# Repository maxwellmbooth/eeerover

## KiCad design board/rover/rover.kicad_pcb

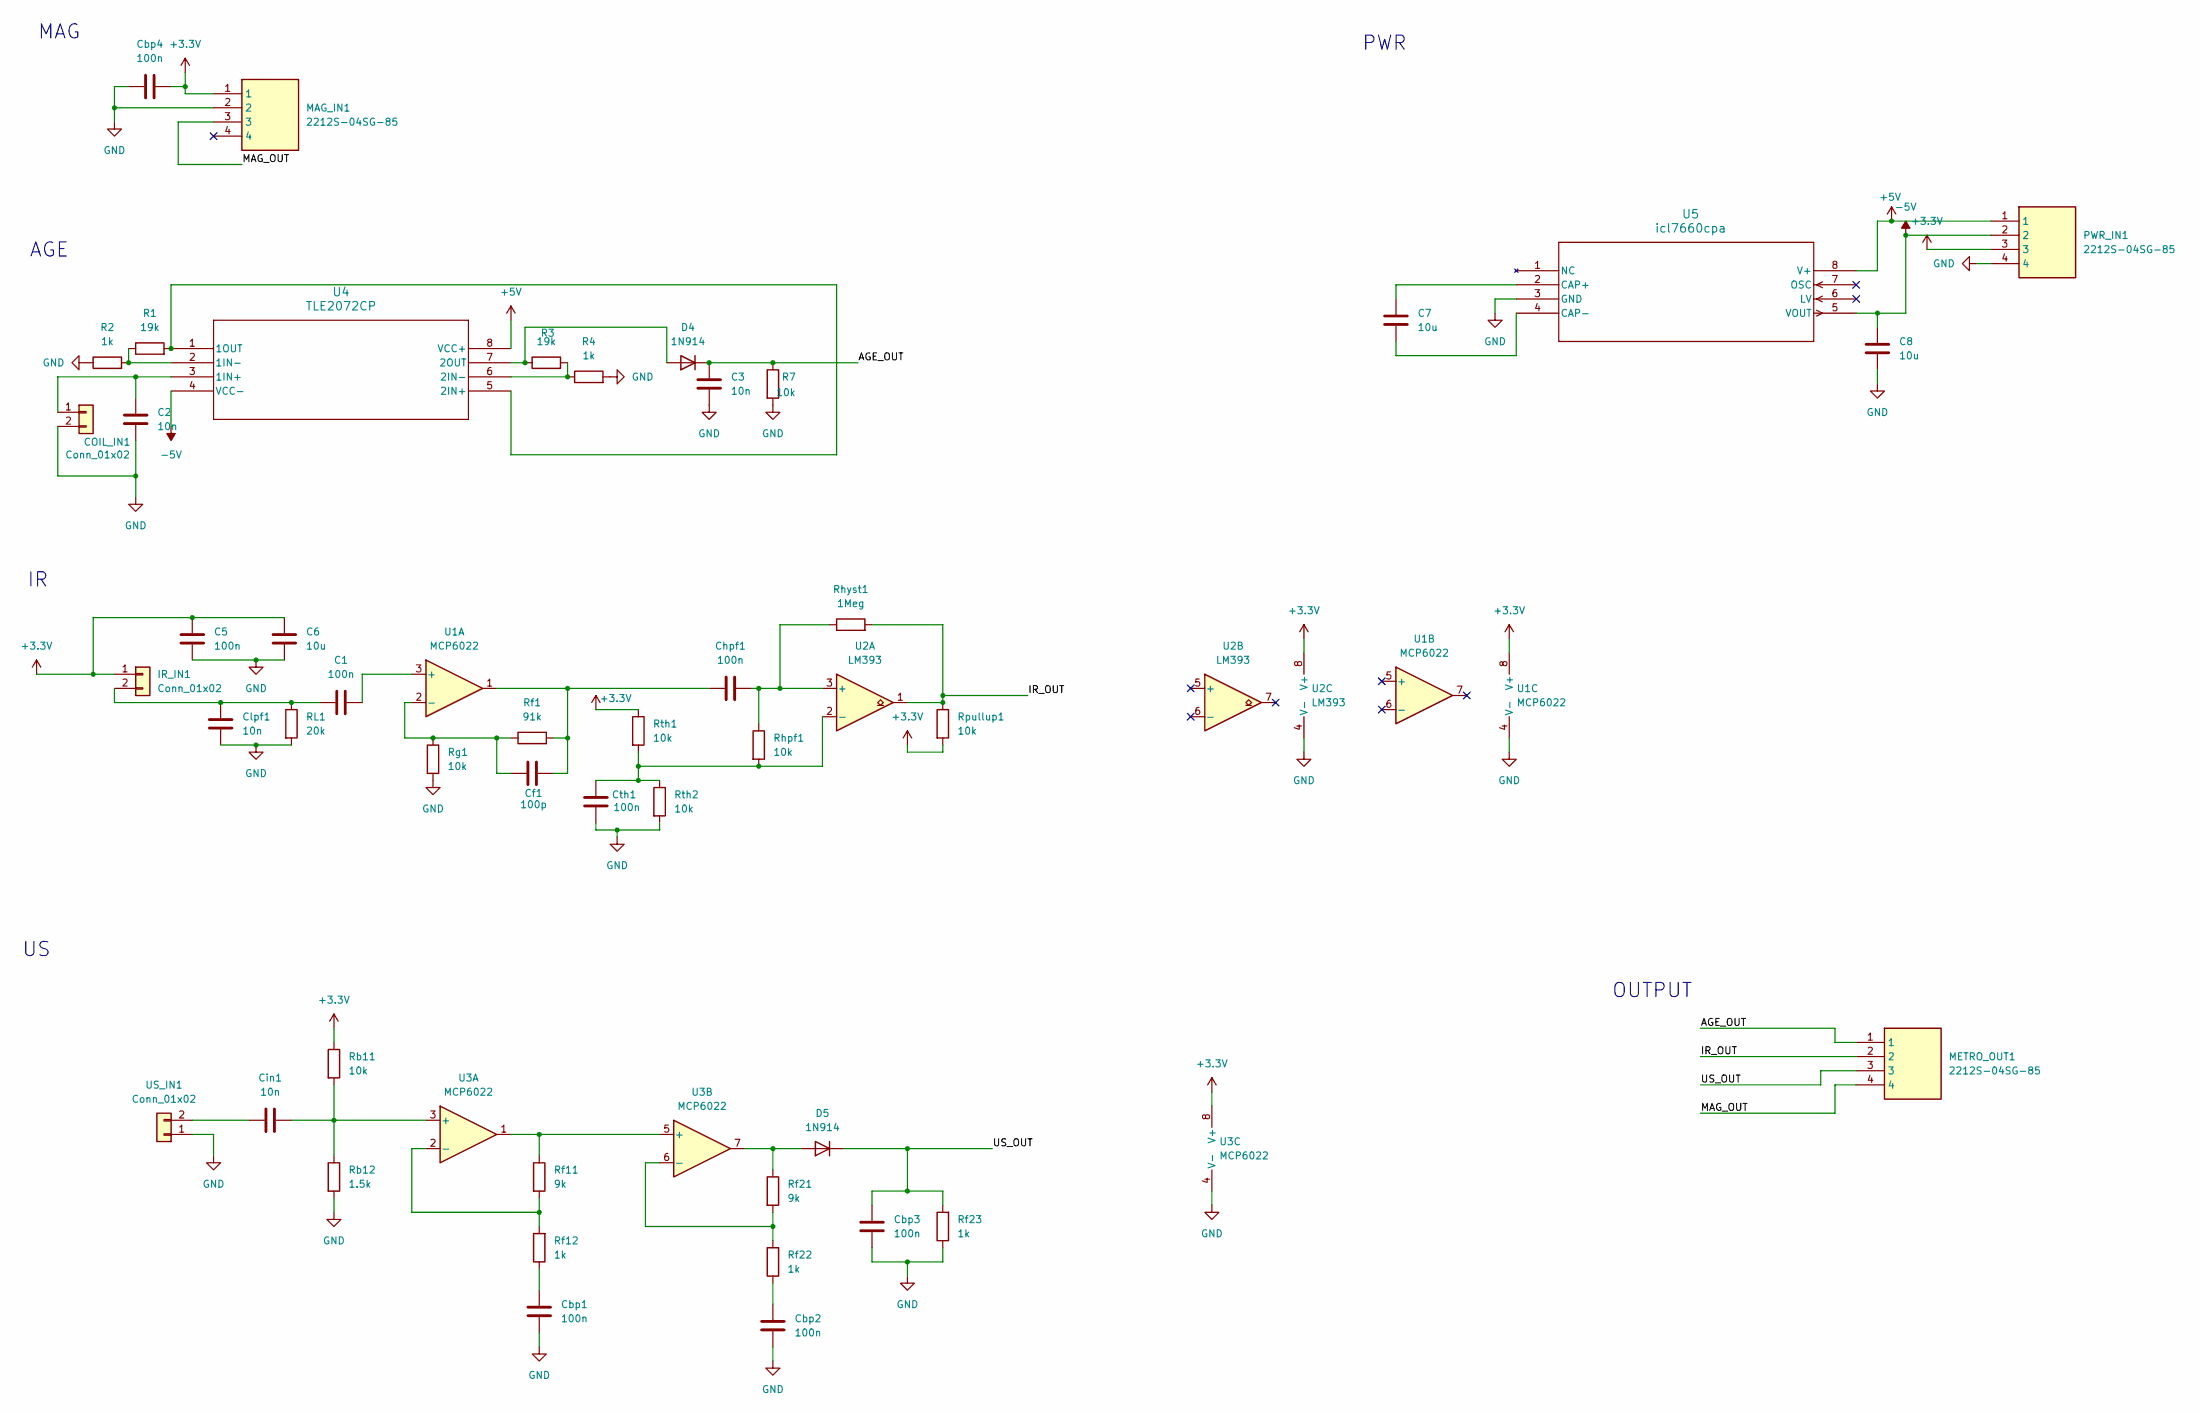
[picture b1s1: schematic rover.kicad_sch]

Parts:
C1, C5: 100n; C_Disc_D5.0mm_W2.5mm_P2.50mm
C2, C3: 10n; C_Disc_D5.0mm_W2.5mm_P2.50mm
C6, C7, C8: 10u; CP_Radial_D5.0mm_P2.50mm
COIL_IN1: Conn_01x02; TerminalBlock_MaiXu_MX126-5.0-02P_1x02_P5.00mm
Cbp1, Cbp2, Cbp3, Cbp4: 100n; C_Disc_D5.0mm_W2.5mm_P2.50mm
Cf1: 100p; C_Disc_D5.0mm_W2.5mm_P2.50mm
Chpf1: 100n; C_Disc_D5.0mm_W2.5mm_P2.50mm
Cin1: 10n; C_Disc_D5.0mm_W2.5mm_P2.50mm
Clpf1: 10n; C_Disc_D5.0mm_W2.5mm_P2.50mm
Cth1: 100n; C_Disc_D5.0mm_W2.5mm_P2.50mm
D4, D5: 1N914; D_DO-35_SOD27_P7.62mm_Horizontal
IR_IN1: Conn_01x02; TerminalBlock_MaiXu_MX126-5.0-02P_1x02_P5.00mm
MAG_IN1: 2212S-04SG-85; 2212S04SG85; Manufacturer_Part_Number 2212S-04SG-85
METRO_OUT1: 2212S-04SG-85; 2212S04SG85; Manufacturer_Part_Number 2212S-04SG-85
PWR_IN1: 2212S-04SG-85; 2212S04SG85; Manufacturer_Part_Number 2212S-04SG-85
R1, R3: 19k; R_Axial_DIN0207_L6.3mm_D2.5mm_P10.16mm_Horizontal
R2, R4: 1k; R_Axial_DIN0207_L6.3mm_D2.5mm_P10.16mm_Horizontal
R7: 10k; R_Axial_DIN0207_L6.3mm_D2.5mm_P10.16mm_Horizontal
RL1: 20k; R_Axial_DIN0207_L6.3mm_D2.5mm_P10.16mm_Horizontal
Rb11: 10k; R_Axial_DIN0207_L6.3mm_D2.5mm_P10.16mm_Horizontal
Rb12: 1.5k; R_Axial_DIN0207_L6.3mm_D2.5mm_P10.16mm_Horizontal
Rf1: 91k; R_Axial_DIN0207_L6.3mm_D2.5mm_P10.16mm_Horizontal
Rf11, Rf21: 9k; R_Axial_DIN0207_L6.3mm_D2.5mm_P10.16mm_Horizontal
Rf12, Rf22, Rf23: 1k; R_Axial_DIN0207_L6.3mm_D2.5mm_P10.16mm_Horizontal
Rg1: 10k; R_Axial_DIN0207_L6.3mm_D2.5mm_P10.16mm_Horizontal
Rhpf1: 10k; R_Axial_DIN0207_L6.3mm_D2.5mm_P10.16mm_Horizontal
Rhyst1: 1Meg; R_Axial_DIN0207_L6.3mm_D2.5mm_P10.16mm_Horizontal
Rpullup1: 10k; R_Axial_DIN0207_L6.3mm_D2.5mm_P10.16mm_Horizontal
Rth1, Rth2: 10k; R_Axial_DIN0207_L6.3mm_D2.5mm_P10.16mm_Horizontal
U1, U3: MCP6022; PDIP8_300MC_MCH
U2: LM393; P8
U4: TLE2072CP; P8
U5: icl7660cpa; 21-0043D_8_MXM
US_IN1: Conn_01x02; TerminalBlock_MaiXu_MX126-5.0-02P_1x02_P5.00mm

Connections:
+3.3V: C5.1, C6.1, Cbp4.2, IR_IN1.1, MAG_IN1.1, PWR_IN1.3, Rb11.1, Rpullup1.2, Rth1.1, U1.8 (V+), U2.8 (V+), U3.8 (V+)
+5V: PWR_IN1.1, U4.8 (VCC+), U5.8 (V+)
-5V: C8.1, PWR_IN1.2, U4.4 (VCC-), U5.5 (VOUT)
/AGE_OUT: C3.1, D4.1 (K), METRO_OUT1.1, R7.1
/IR_OUT: METRO_OUT1.2, Rhyst1.2, Rpullup1.1, U2.1
/MAG_OUT: MAG_IN1.3, METRO_OUT1.4
/US_OUT: Cbp3.1, D5.1 (K), METRO_OUT1.3, Rf23.2
GND: C2.2, C3.2, C5.2, C6.2, C8.2, COIL_IN1.2, Cbp1.2, Cbp2.2, Cbp3.2, Cbp4.1, Clpf1.2, Cth1.2, MAG_IN1.2, PWR_IN1.4, R2.1, R4.2, R7.2, RL1.2, Rb12.2, Rf23.1, Rg1.2, Rth2.2, U1.4 (V-), U2.4 (V-), U3.4 (V-), U5.3 (GND), US_IN1.1
unnamed: C2.1, COIL_IN1.1, U4.3 (1IN+)
unnamed: Cbp1.1, Rf12.1
unnamed: Cbp2.1, Rf22.1
unnamed: Cf1.2, Chpf1.1, Rf1.2, U1.1
unnamed: D4.2 (A), R3.1, U4.7 (2OUT)
unnamed: D5.2 (A), Rf21.1, U3.7
unnamed: C1.1, Clpf1.1, IR_IN1.2, RL1.1
unnamed: C1.2, U1.3 (+)
unnamed: Cf1.1, Rf1.1, Rg1.1, U1.2 (-)
unnamed: Chpf1.2, Rhpf1.1, Rhyst1.1, U2.3 (+)
unnamed: Cth1.1, Rhpf1.2, Rth1.2, Rth2.1, U2.2 (-)
unnamed: Cin1.1, Rb11.2, Rb12.1, U3.3 (+)
unnamed: Rf11.2, Rf12.2, U3.2 (-)
unnamed: Rf11.1, U3.1, U3.5 (+)
unnamed: Rf21.2, Rf22.2, U3.6 (-)
unnamed: R1.1, R2.2, U4.2 (1IN-)
unnamed: R1.2, U4.1 (1OUT), U4.5 (2IN+)
unnamed: R3.2, R4.1, U4.6 (2IN-)
unnamed: C7.1, U5.2 (CAP+)
unnamed: C7.2, U5.4 (CAP-)
unnamed: Cin1.2, US_IN1.2

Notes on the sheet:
PWR
AGE
OUTPUT
MAG

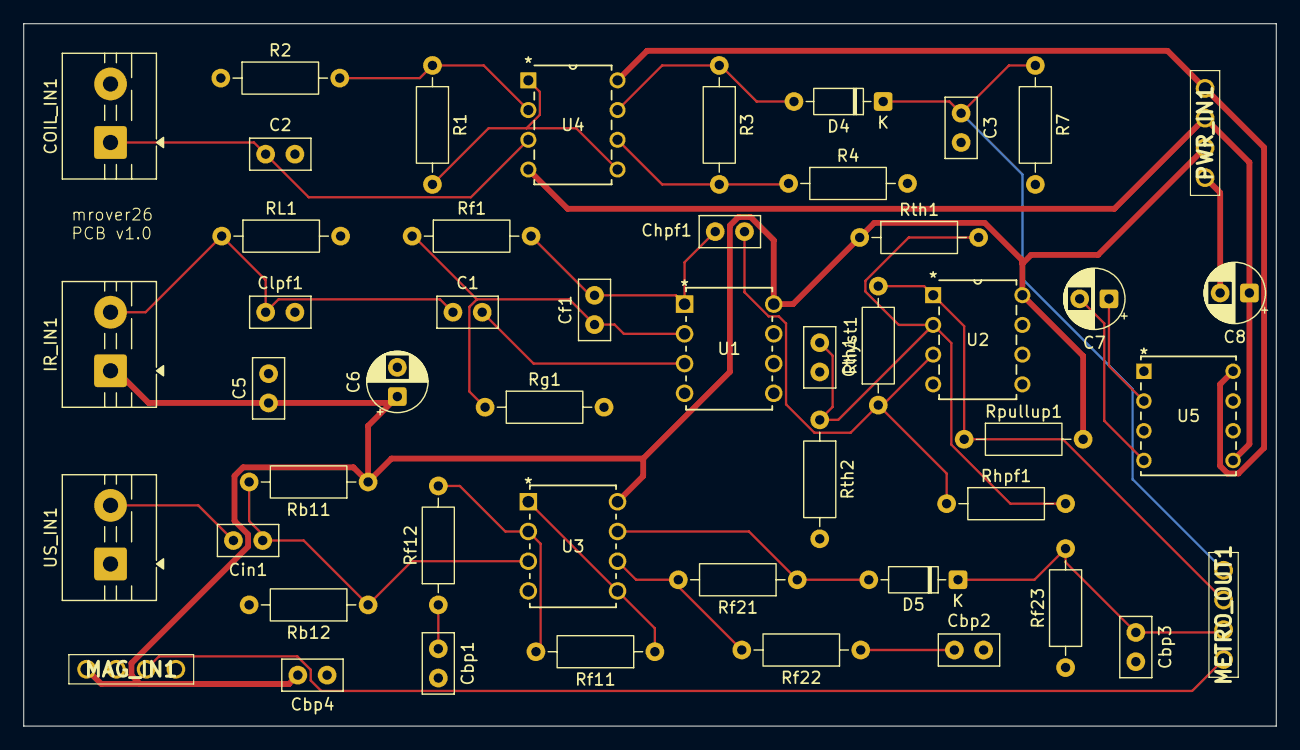
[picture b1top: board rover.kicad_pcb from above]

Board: 2 copper layers, 107.0 x 60.0 mm, 49 parts (0 on the bottom side), 29 nets.

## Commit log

2026-05-13 second commit
2026-05-13 Added PIO files
2026-05-13 Setup basic web server
2026-05-18 Started UDP transmission protocol and added controller main
2026-05-19 Final commit to double arduino idea.
2026-05-19 Final commit to double arduino idea
2026-05-19 Started pygame app
2026-05-20 Rover control working
2026-05-28 Added bidirectional UDP support and started PCB design
2026-06-03 Merged IR code
2026-06-03 Changed UDP print to write
2026-06-04 Finished PCB
2026-06-05 Added -5V generation to PCB
2026-06-07 Updated UI for app.
2026-06-10 Finished merging rover-side code and made small changes to app
2026-06-10 Added UDP reset and auto-reset and fixed transmission bugs.
2026-06-16 Changed thresholds and added rock type panel in app
